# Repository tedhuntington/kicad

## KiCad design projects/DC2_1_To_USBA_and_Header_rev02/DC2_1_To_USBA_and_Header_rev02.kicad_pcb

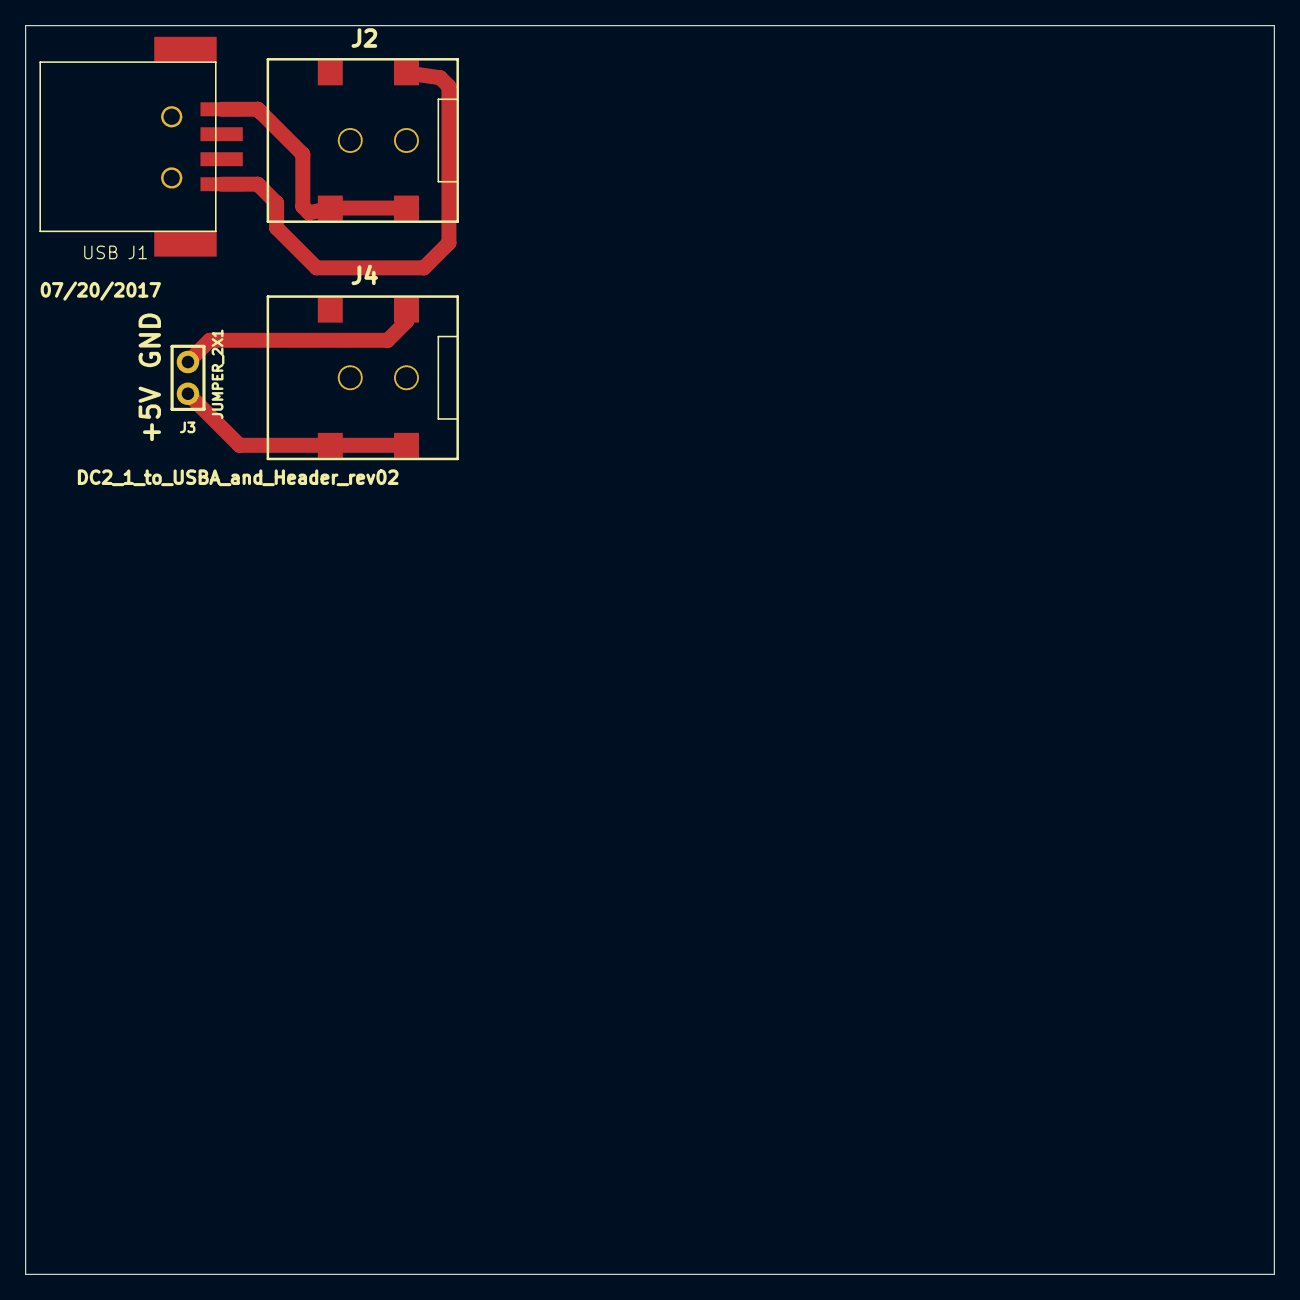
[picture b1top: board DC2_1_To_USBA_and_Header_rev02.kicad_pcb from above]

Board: 2 copper layers, 100.0 x 100.0 mm, 4 parts (0 on the bottom side), 4 nets.

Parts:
J1: USB; TED_USB_A_SMD
J2, J4: DC_2.1mm_3pin; TED_2.1mm_DC_SMD
J3: JUMPER_2X1; TED_HEADER_2x1

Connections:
unnamed: J1.1, J2.1
unnamed: J1.4, J2.2
unnamed: J3.1, J4.1
unnamed: J3.2, J4.2

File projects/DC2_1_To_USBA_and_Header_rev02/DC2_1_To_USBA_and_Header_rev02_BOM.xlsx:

DC2_1_To_USBA_and_Header_rev02
Thu 20 Jul 2017 09:30:34 PM PDT
Eeschema 4.0.6-e0-6349~53~ubuntu16.04.1
Component Count:4
Ref | Qnty | Value | Part | Part# | Unit Cost | Total Cost | Major Distributor | Minor Distributor
J1, | 1 | USB | connectors:USB_A_SMD | Molex 48037-1000 | 1.11 | 1.11 | Mouser/Newark | AliExpress/Ebay
J2, J4, | 2 | DC_2.1mm_3pin | connectors:2.1mm_DC_SMD | Switchcraft RASM722X | 1.12 | 2.24 | Mouser/Digi-Key | AliExpress/Ebay
J3, | 1 | JUMPER_2X1 | connectors:HEADER_2x1 | FCI 68000-102HLF | 0.19 | 0.19 | Digi-Key | AliExpress/Ebay
Total Cost |  |  |  |  |  | 3.54

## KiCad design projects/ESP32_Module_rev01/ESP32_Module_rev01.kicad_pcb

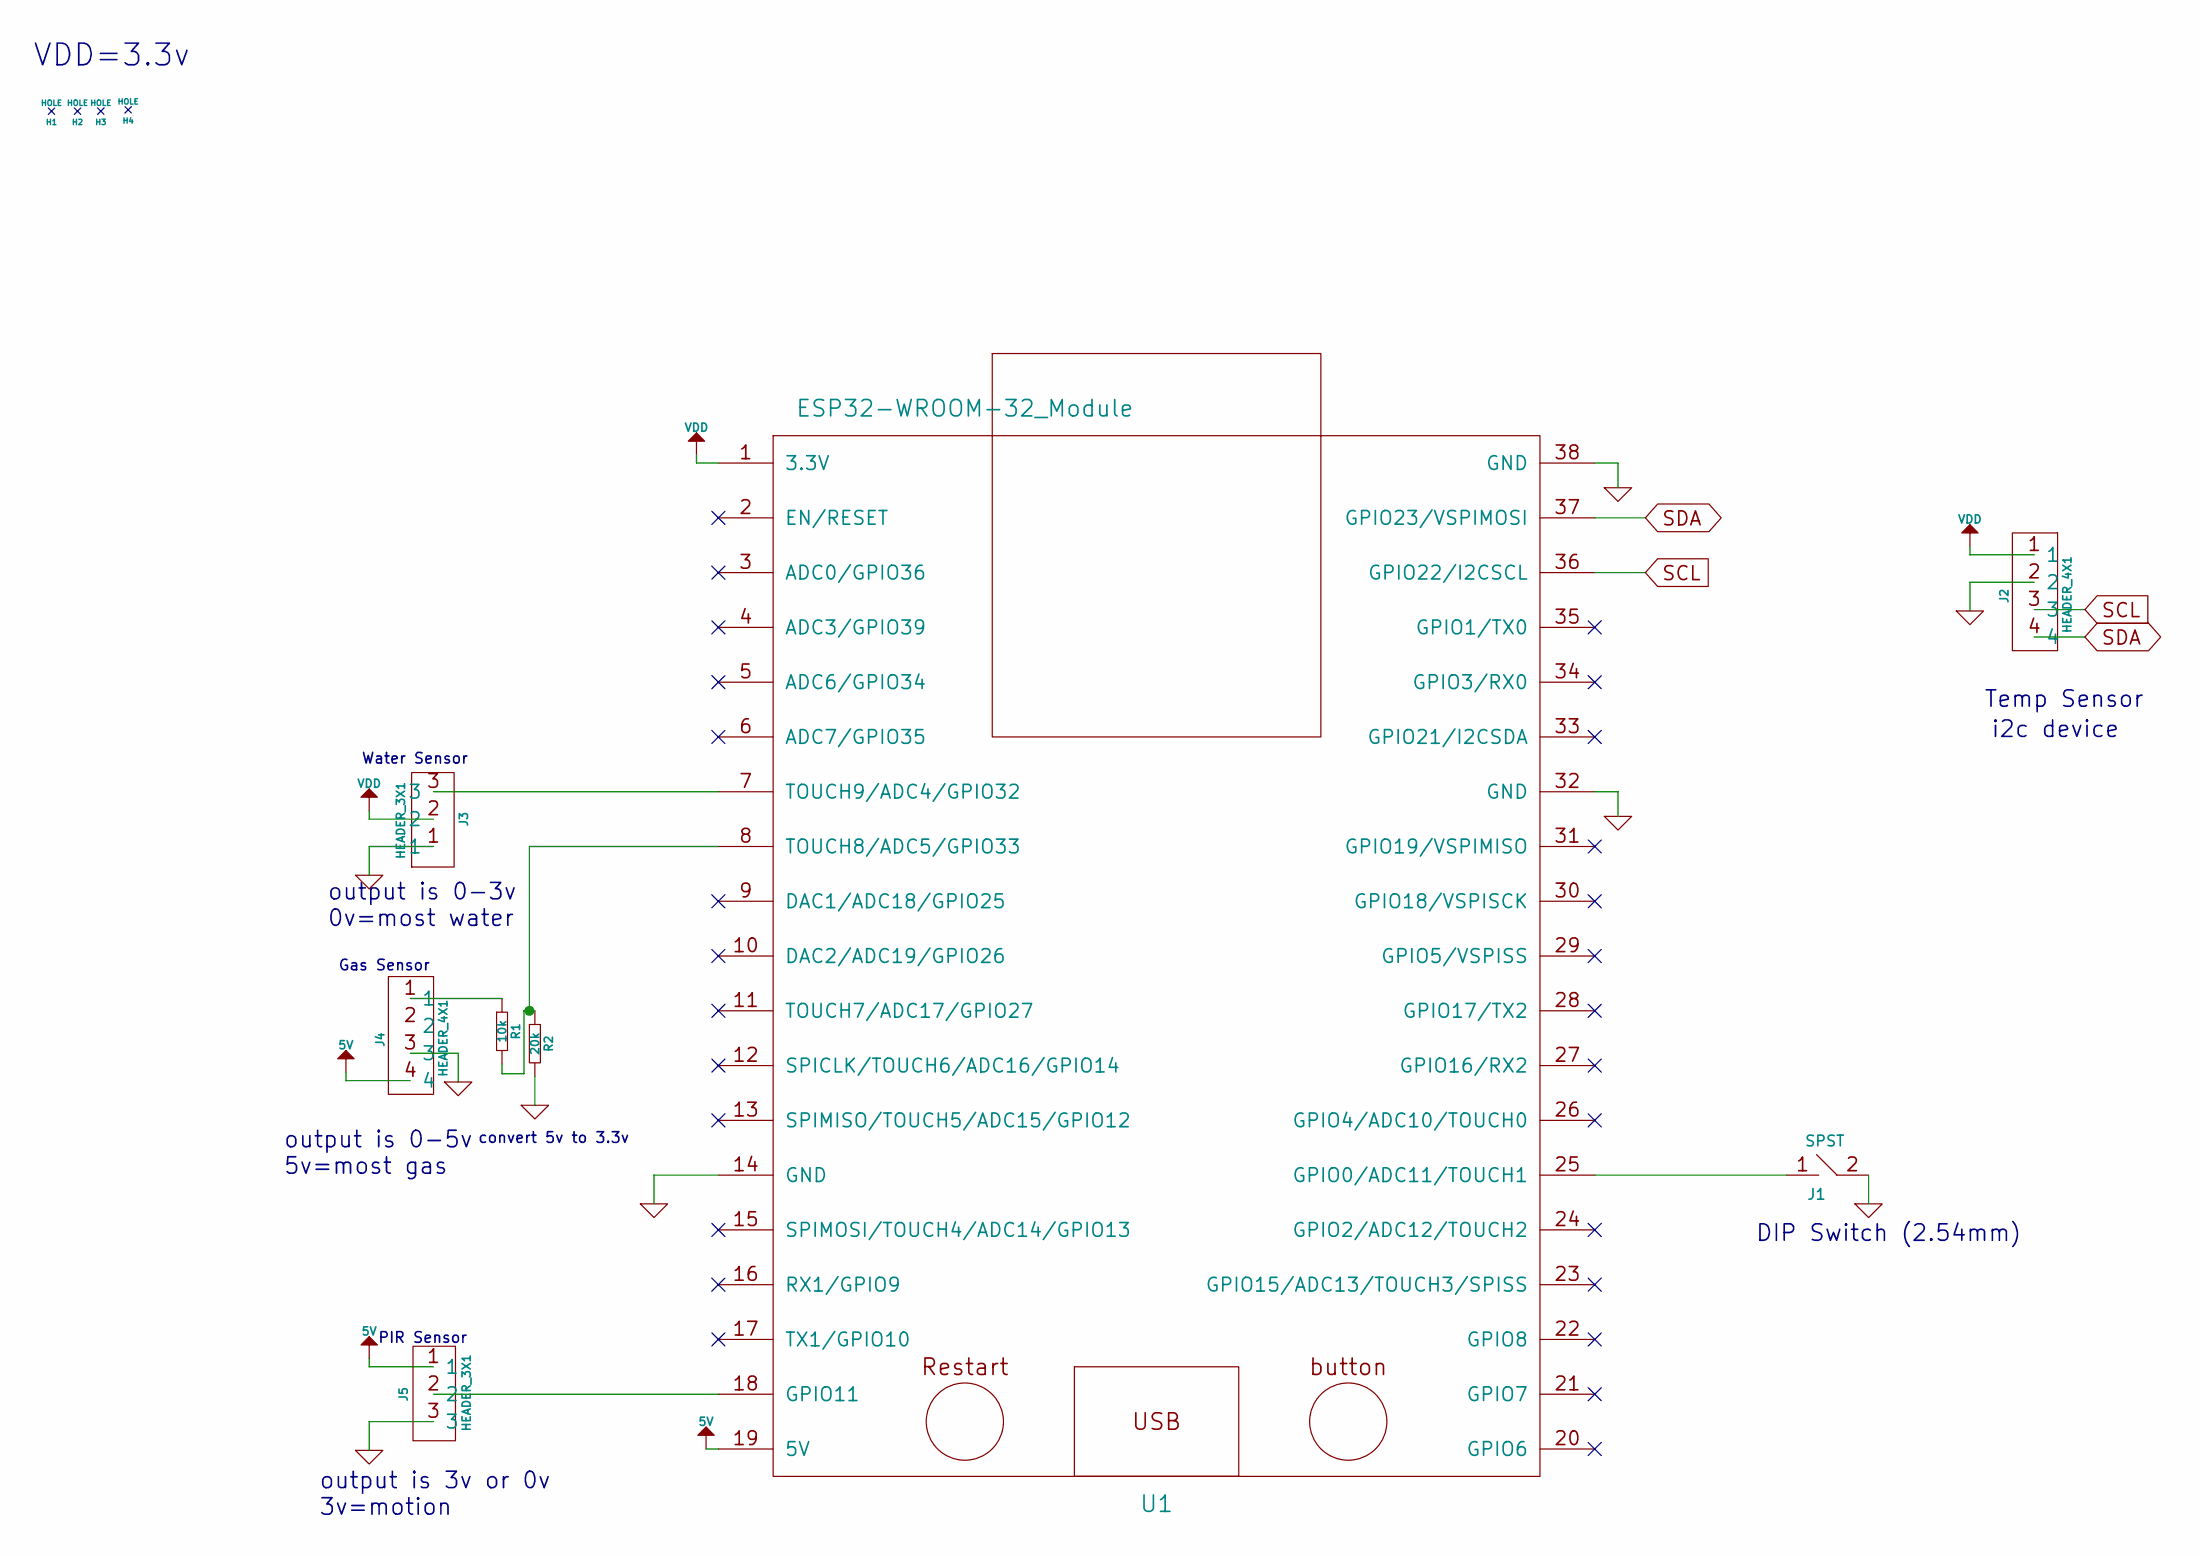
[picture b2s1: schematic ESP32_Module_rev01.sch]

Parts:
H1, H2, H3, H4: HOLE; TED_Hole_3mm
J1: SPST; TED_DIPSWITCH_1
J2, J4: HEADER_4X1; TED_HEADER_4x1
J3, J5: HEADER_3X1; TED_HEADER_3x1
R1: 10k; TED_SM0603_R
R2: 20k; TED_SM0603_R
U1: ESP32-WROOM-32_Module; TED_ESP32_Module_38pin

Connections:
5V: J4.4, J5.1, U1.19 (5V)
GND: J1.2, J2.2, J3.1, J4.3, J5.3, R2.2, U1.14 (GND), U1.32 (GND), U1.38 (GND)
unnamed: J1.1, U1.25 (GPIO0/ADC11/TOUCH1)
unnamed: J3.3, U1.7 (TOUCH9/ADC4/GPIO32)
unnamed: J4.1, R1.1
unnamed: J5.2, U1.18 (GPIO11)
unnamed: R1.2, R2.1, U1.8 (TOUCH8/ADC5/GPIO33)
SCL: J2.3, U1.36 (GPIO22/I2CSCL)
SDA: J2.4, U1.37 (GPIO23/VSPIMOSI)
VDD: J2.1, J3.2, U1.1 (3.3V)

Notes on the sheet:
VDD=3.3v
Water Sensor
DIP Switch (2.54mm)
PIR Sensor
Temp Sensor
output is 3v or 0v 3v=motion
output is 0-3v 0v=most water
i2c device
Gas Sensor
output is 0-5v 5v=most gas
convert 5v to 3.3v

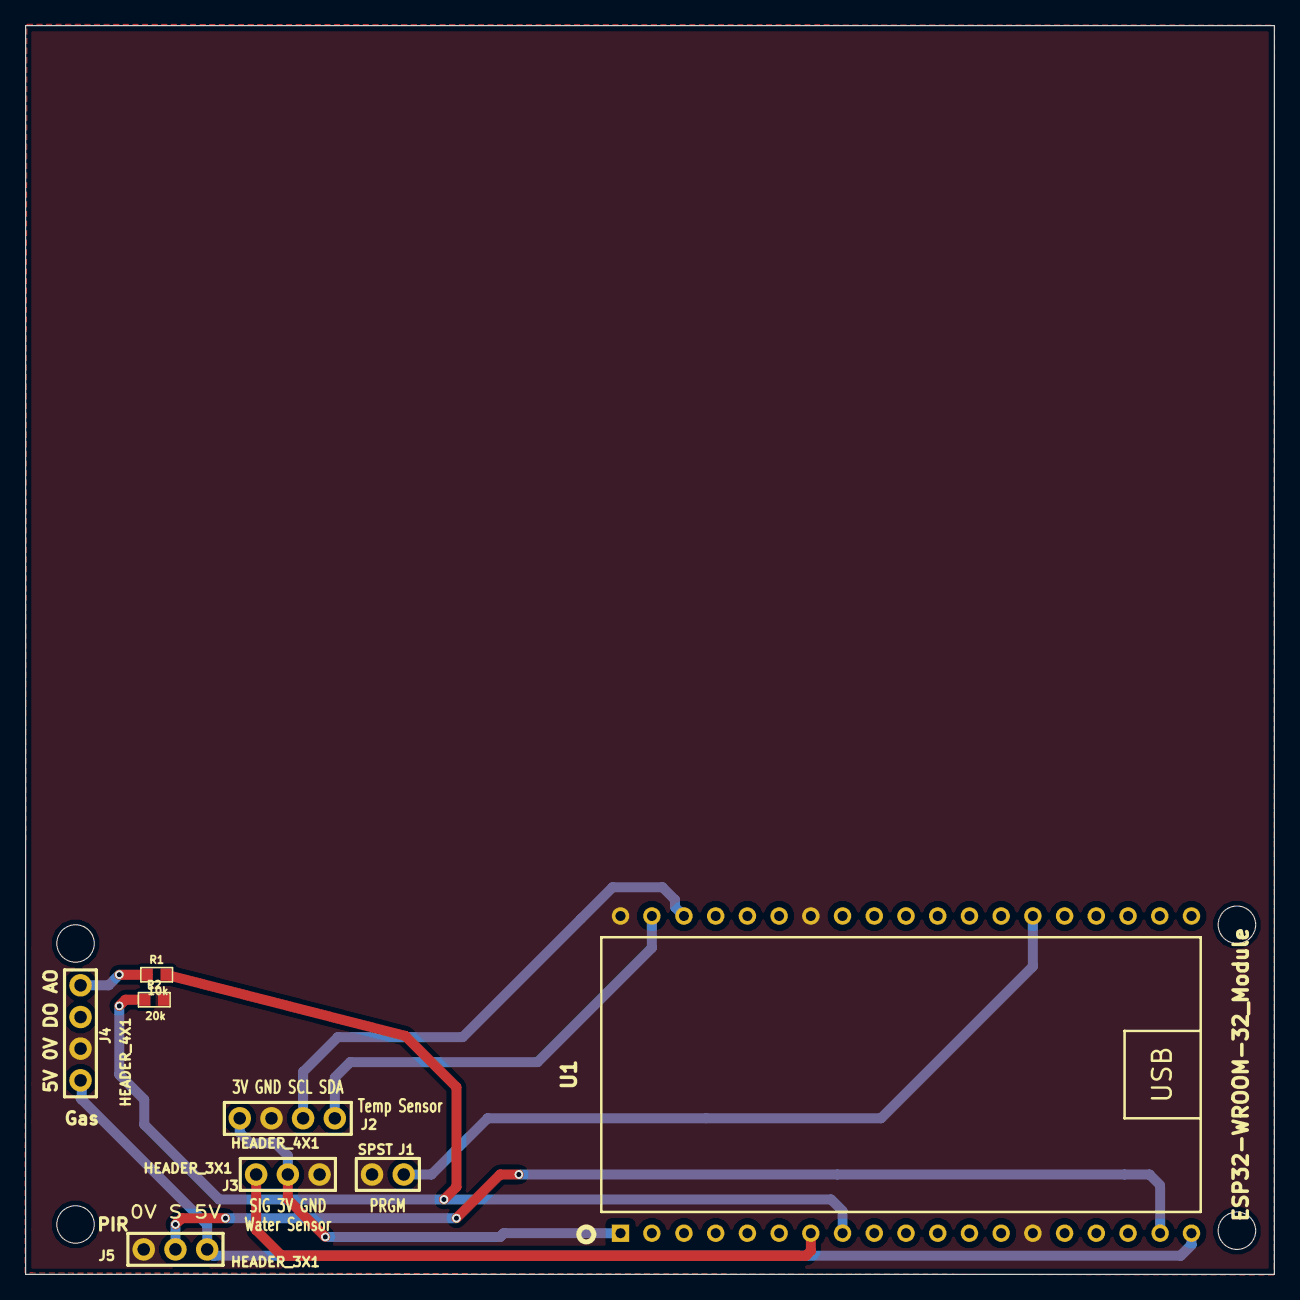
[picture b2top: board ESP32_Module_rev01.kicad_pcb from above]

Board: 2 copper layers, 100.0 x 100.0 mm, 12 parts (0 on the bottom side), 10 nets.
